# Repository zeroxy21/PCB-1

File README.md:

# PCB-1
Open the files with KiCad or any dedicated program

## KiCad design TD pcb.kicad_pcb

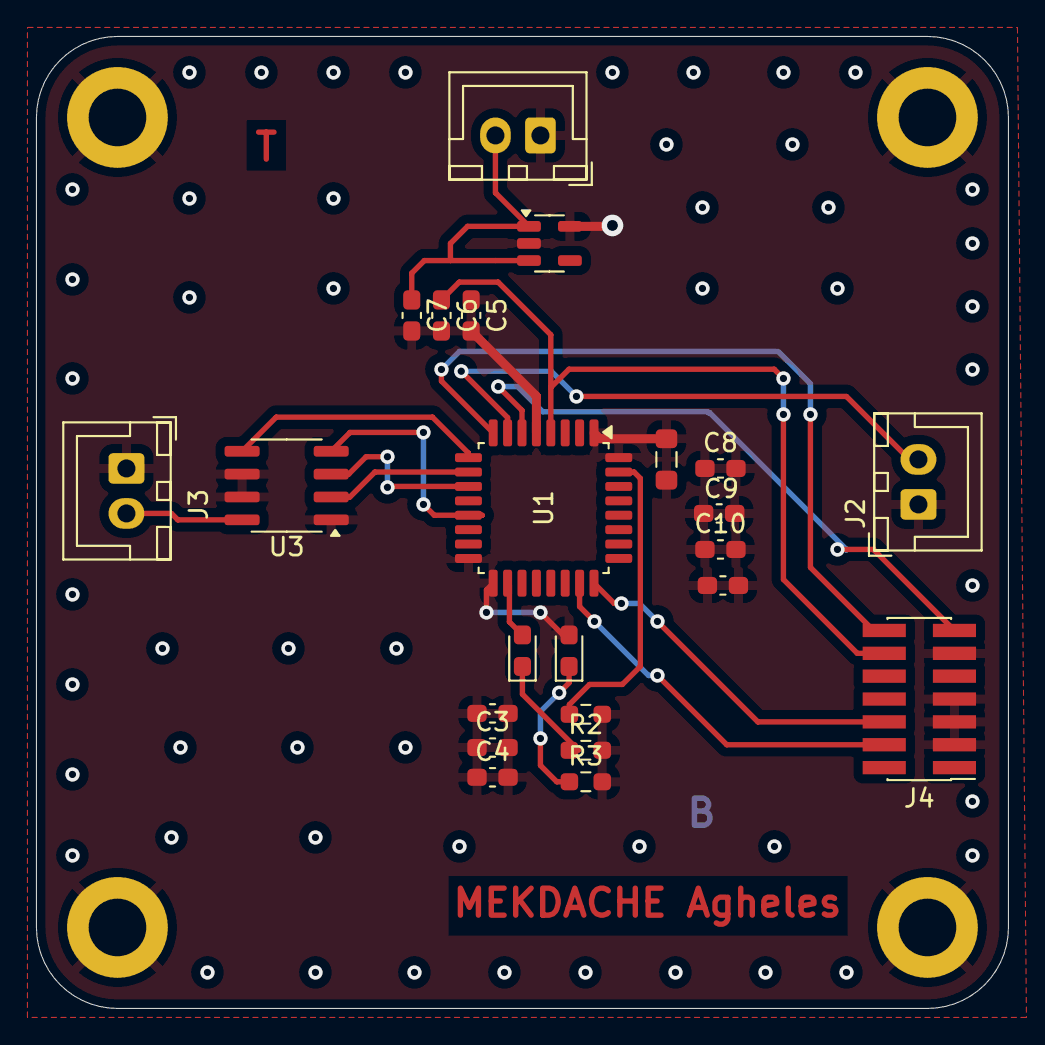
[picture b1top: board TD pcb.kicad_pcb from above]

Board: 2 copper layers, 54.0 x 54.0 mm, 27 parts (0 on the bottom side), 17 nets.

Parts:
C1, C10: 10u; C_0603_1608Metric_Pad1.08x0.95mm_HandSolder
C2, C3, C5, C6, C9: 100n; C_0603_1608Metric_Pad1.08x0.95mm_HandSolder
C4, C7, C8: 1u; C_0603_1608Metric_Pad1.08x0.95mm_HandSolder
D1, D2: LED; D_0603_1608Metric_Pad1.05x0.95mm_HandSolder
H1, H2, H3, H4: MountingHole_Pad; MountingHole_3.2mm_M3_DIN965_Pad
J1: Power; JST_XH_B2B-XH-A_1x02_P2.50mm_Vertical
J2: Analog input; JST_XH_B2B-XH-A_1x02_P2.50mm_Vertical
J3: Analog output; JST_XH_B2B-XH-A_1x02_P2.50mm_Vertical
J4: ST-Link; PinHeader_2x07_P1.27mm_Vertical_SMD
L1: 39n; L_0805_2012Metric_Pad1.05x1.20mm_HandSolder
R1: 10k; R_0603_1608Metric_Pad0.98x0.95mm_HandSolder
R2, R3: 1k; R_0603_1608Metric_Pad0.98x0.95mm_HandSolder
U1: STM32L021K4Tx; LQFP-32_7x7mm_P0.8mm
U2: MCP1802x-xx02xOT; SOT-23-5
U3: MCP4801; SOIC-8_3.9x4.9mm_P1.27mm

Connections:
5V: C7.1, J1.2, U2.1 (VIN), U2.3 (~SHDN)
/LED_Status: D1.2 (A), U1.18 (PA8)
ADC_IN1: J2.2, U1.7 (PA1)
DAC_OUT: J3.2, U3.8 (Vout)
DAC_nCS: U1.10 (PA4), U3.2 (~CS)
DAC_nLDAC: U1.9 (PA3), U3.5 (~LDAC)
GND: C1.1, C1.2, C2.1, C2.2, C3.1, C3.2, C4.1, C4.2, C5.1, C5.2, C6.2, C7.2, C8.1, C8.2, C9.1, C9.2, C10.1, C10.2, D2.2 (A), H1.1, H2.1, H3.1, H4.1, J1.1, J2.1, J3.1, J4.3, J4.5, J4.7, J4.11, L1.1, L1.2, R1.2, R2.2, R3.2, U1.1 (VDD), U1.5 (VDDA), U1.16 (VSS), U1.17 (VDD), U1.32 (VSS), U2.2 (GND), U2.5 (VOUT), U3.1 (Vdd), U3.6 (~SHDN), U3.7 (Vss)
NRST: C6.1, J4.12, U1.4 (NRST)
unnamed: D1.1 (K), R2.1
unnamed: D2.1 (K), R3.1
unnamed: R1.1, U1.31 (PB9)
SPI1_MOSI: U1.13 (PA7), U3.4 (SDI)
SPI1_SCK: U1.11 (PA5), U3.3 (SCK)
SYS_SWCLK: J4.6, U1.24 (PA14)
SYS_SWDIO: J4.4, U1.23 (PA13)
USART2_RX: J4.13, U1.6 (PA0)
USART2_TX: J4.14, U1.8 (PA2)
